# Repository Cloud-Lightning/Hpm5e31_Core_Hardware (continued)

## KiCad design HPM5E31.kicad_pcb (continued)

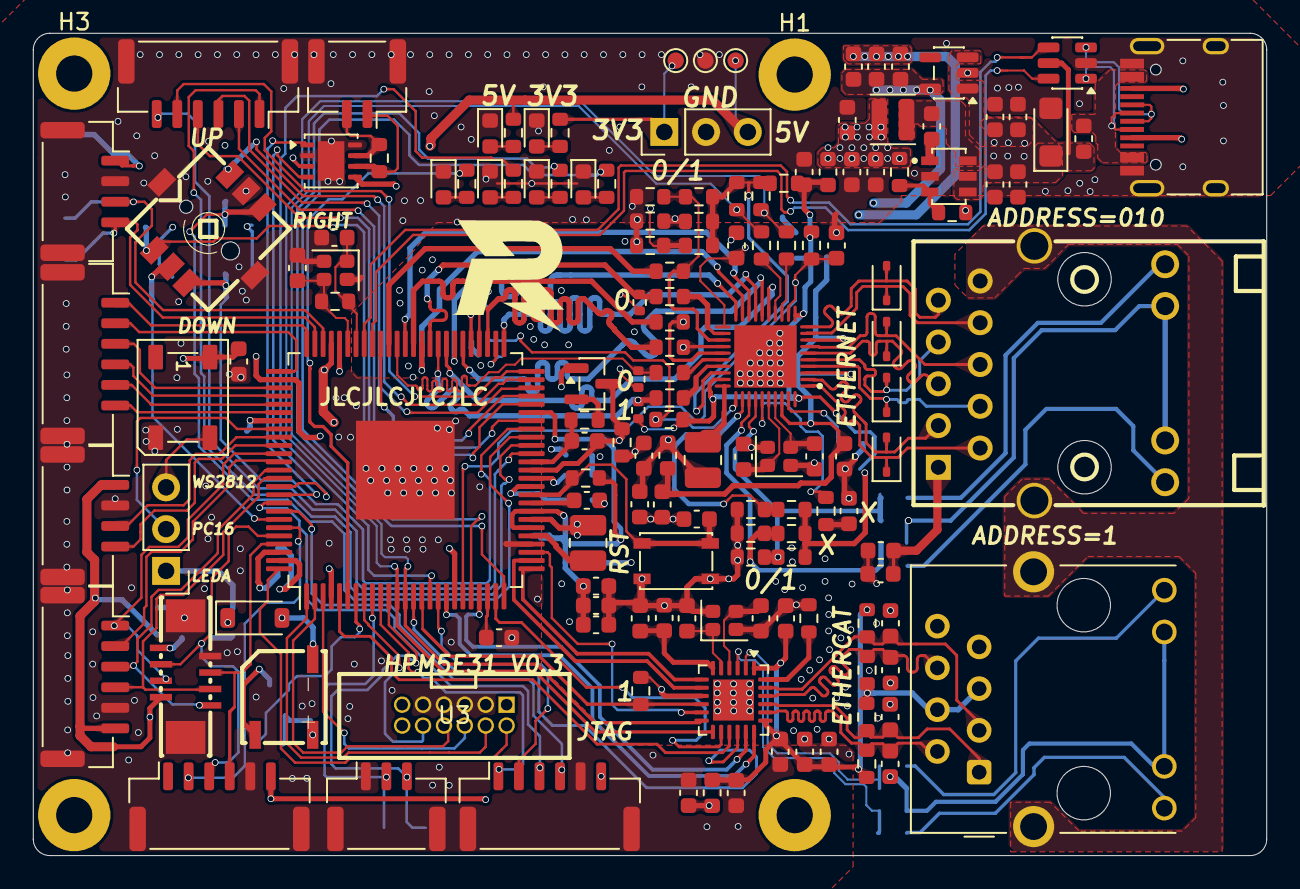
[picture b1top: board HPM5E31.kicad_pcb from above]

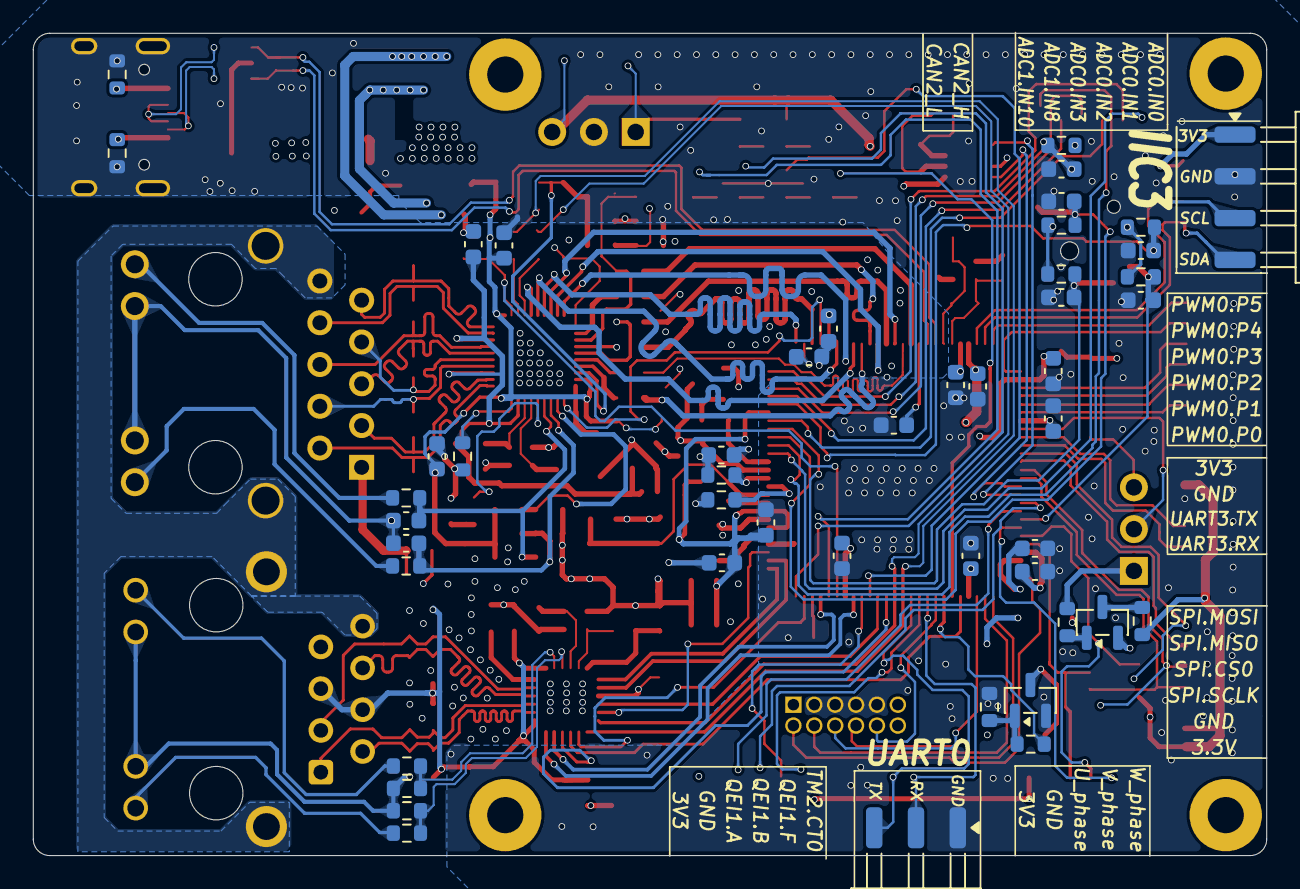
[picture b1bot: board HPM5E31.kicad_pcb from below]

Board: 4 copper layers, 75.0 x 50.0 mm, 200 parts (48 on the bottom side), 161 nets.

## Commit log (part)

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2026-06-09 Update KiCad project files
